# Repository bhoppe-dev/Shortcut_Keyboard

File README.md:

# Shortcut Keyboard

A programmable macro keyboard project featuring 8 customizable keys and a rotary encoder for volume control. Built with an RP2040 microcontroller and Cherry MX switches.

<p align="center">
  
  <br>
  <em>Shortcut Keyboard PCB</em>
</p>

## Features

- 8 programmable macro keys with Cherry MX switches (Blue or Brown)
- Rotary encoder with push button for volume control/mute
- USB-C connectivity
- RP2040 microcontroller
- CircuitPython firmware
- Windows compatibility
- Up to 3 different profiles for key configurations
- No additional drivers required

## Specifications

| Parameter | Value |
|-----------|-------|
| Input Voltage | 4.75-5.25V (USB) |
| Operating Current | ~50mA |
| Operating Temperature | 0-85°C |
| PCB Dimensions | 100 x 79 mm |
| Switches | Cherry MX Blue/Brown |
| Communication | USB HID |
| MCU | RP2040 |
| Firmware | CircuitPython |

## Hardware

The keyboard consists of three PCBs:
1. Main board with RP2040 and components
2. Top plate
3. Bottom plate

### Key Switch Options

| Feature | MX Blue | MX Brown |
|---------|---------|----------|
| Actuation Force | 60 cN | 55 cN |
| Pre-travel | 2.2 mm | 2.0 mm |
| Total Travel | 4.0 mm | 4.0 mm |
| Characteristics | Tactile & Clicky | Tactile |
| Sound | Audible click | Silent |

## Software

> The source code is available on GitHub at [https://github.com/bhoppe-dev/ShortcutKeyboardApp](https://github.com/bhoppe-dev/ShortcutKeyboardApp).
> 
The software suite includes:
- Windows configuration application
- Three customizable profiles
- File/folder/application launch capabilities
- URL opening support
- System tray integration
- Dark mode support

<p align="center">
  
  <br>
  <em>Main Window</em>
</p>

<p align="center">
  
  <br>
  <em>Configuration Window</em>
</p>

## Firmware

The keyboard runs CircuitPython firmware with the following features:
- USB HID implementation
- Key debouncing
- Rotary encoder support
- Volume control integration
- Multiple profile support

## License

This project is licensed under the BSD 2-Clause License - see the LICENSE file for details.

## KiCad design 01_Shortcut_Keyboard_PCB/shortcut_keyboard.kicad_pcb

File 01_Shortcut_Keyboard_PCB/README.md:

# PCB Documentation

KiCad project files for the Shortcut-Keyboard PCB based on RP2040.

## RP2040 Interface Block Diagram
Interface overview of the used RP2040 microcontroller pins and buses:

<p align="center">
  
  <br>
  <em>RP2040 Microcontroller Interface</em>
</p>

## Directory Structure

### Folders
- `01_Schematic/` - Schematic exports and documentation
- `02_BOM/` - Bill of Materials and part lists
- `03_STEP/` - 3D models and mechanical files

### KiCad Files
- `shortcut_keyboard.kicad_pro` - Project file
- `shortcut_keyboard.kicad_sch` - Main schematic
- `shortcut_keyboard.kicad_pcb` - PCB layout
- `MCU.kicad_sch` - MCU specific schematic
- `Connector.kicad_sch` - Connector specific schematic
- `Revision_History.kicad_sch` - Version tracking

## Layer Stackup
This PCB uses a SIG/GND/VCC/SIG stackup instead of the more conventional SIG/GND/GND/SIG configuration. This decision was based on several design considerations:

1. **Design Optimization:** The chosen stackup provides an optimal balance between routing efficiency and performance for this specific application.

2. **Signal Requirements Analysis:** After analyzing the signal integrity requirements for the RP2040-based keyboard, I determined that the modest-speed signals don't demand the theoretical advantages of dual ground planes.

3. **Power Distribution:** The dedicated VCC plane on L3 provides sufficient power distribution for all components while simplifying the overall routing strategy.

4. **Manufacturing Considerations:** The SIG/GND/VCC/SIG configuration maintains the same manufacturing complexity while offering adequate electrical performance for this application.

5. **Application-Specific Design:** For this particular keyboard application, the SIG/GND/VCC/SIG arrangement meets all functional requirements while enabling a more streamlined development process.

## Specifications
- Size: 100 x 79 mm
- Layers: 4 layer, 1.6mm FR4
- Version: V1.00.01 (2025-02-02)
- KiCad Version: 8.0.7

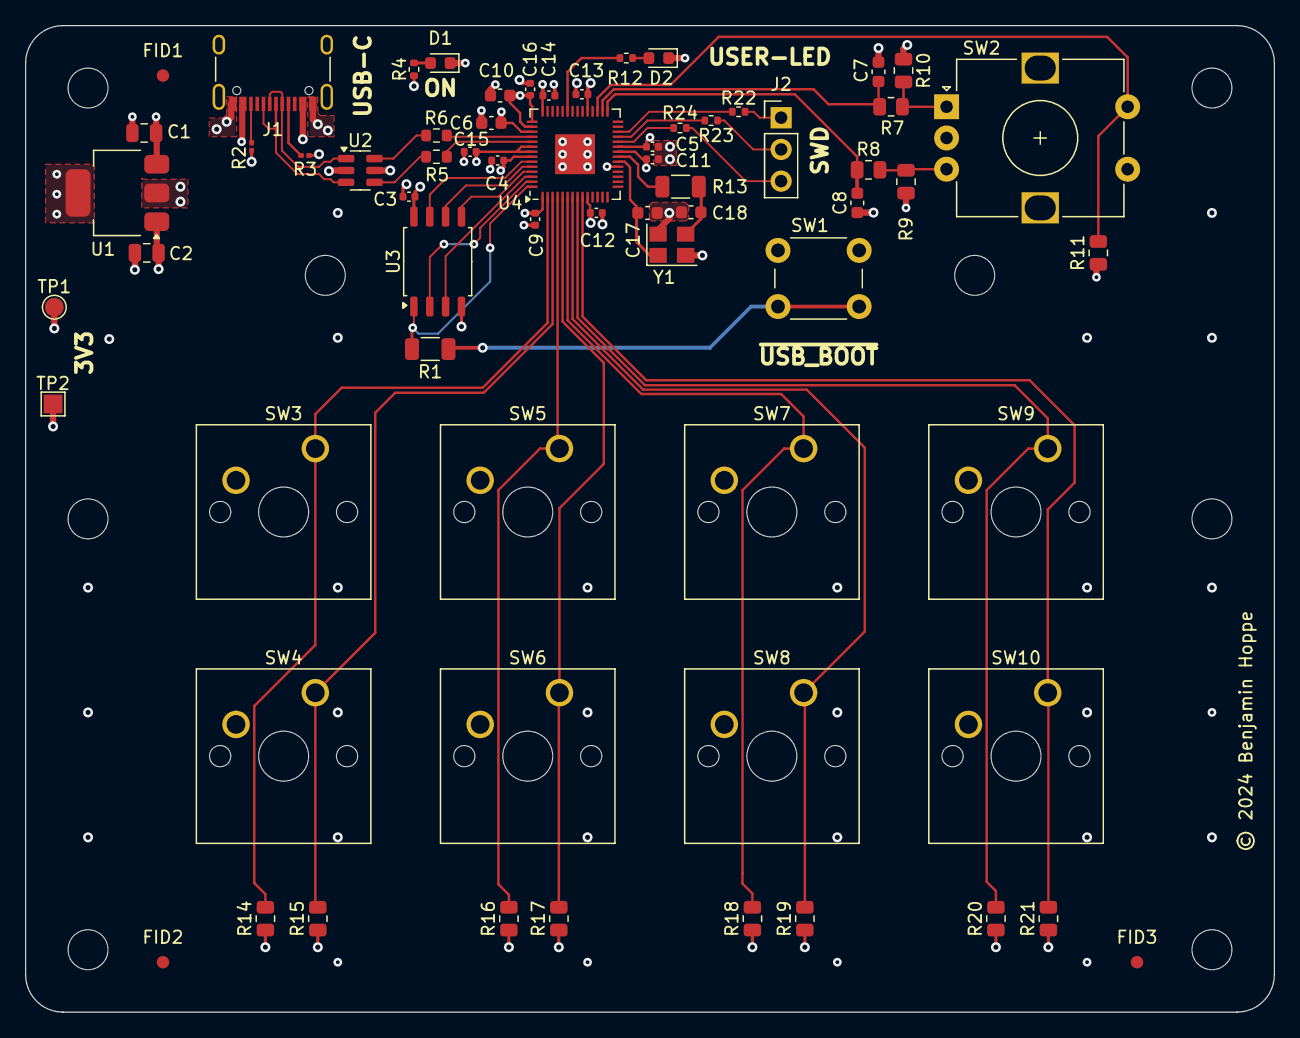
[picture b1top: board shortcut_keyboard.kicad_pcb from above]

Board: 4 copper layers, 100.0 x 79.0 mm, 74 parts (0 on the bottom side), 44 nets.

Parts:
C1, C2: 10uF; C_0805_2012Metric
C3, C4, C5, C9, C11, C12, C13, C14, C15, C16: 100nF; C_0402_1005Metric
C6, C10: 1uF; C_0603_1608Metric
C7, C8: 10nF; C_0603_1608Metric
C17, C18: 15pF; C_0603_1608Metric
D1: SML-D12Y8WT86R (yellow); LED_0603_1608Metric
D2: KT-0603R (red); LED_0603_1608Metric
FID1, FID2, FID3: Fiducial; Fiducial_1mm_Mask2mm
H1, H2, H3, H4, H5, H6, H7, H8: MountingHole; MountingHole_3.2mm_M3
J1: USB_C_Receptacle_USB2.0_16P; USB_C_Receptacle_XKB_U262-16XN-4BVC11
J2: Conn_01x03; PinHeader_1x03_P2.54mm_Vertical
R1, R13: 1k; R_1206_3216Metric
R2, R3: 5k1; R_0201_0603Metric
R4: 220; R_0402_1005Metric
R5, R6: 27; R_0603_1608Metric
R7, R8, R9, R10, R11, R14, R15, R16, R17, R18, R19, R20, R21: 10k; R_0805_2012Metric
R12: 470; R_0402_1005Metric
R22, R23, R24: 49R9; R_0402_1005Metric
SW1: SW_Push; SW_PUSH_6mm_H5mm
SW2: RotaryEncoder_Switch; RotaryEncoder_Alps_EC12E-Switch_Vertical_H20mm
SW3, SW4, SW5, SW6, SW7, SW8, SW9, SW10: SW_Push; SW_Cherry_MX_1.00u_PCB
TP1: TP_3V3; TestPoint_Pad_D1.5mm
TP2: TP_GND; TestPoint_Pad_1.5x1.5mm
U1: NCP1117-3.3_SOT223; SOT-223-3_TabPin2
U2: USBLC6-2SC6; SOT-23-6
U3: W25Q128JVS; SOIC-8_5.23x5.23mm_P1.27mm
U4: RP2040; QFN-56-1EP_7x7mm_P0.4mm_EP3.2x3.2mm
Y1: ABM8-272-T3; Crystal_SMD_3225-4Pin_3.2x2.5mm

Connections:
+1V1: C4.1, C5.1, C6.1, U4.23 (DVDD), U4.45 (VREG_VOUT), U4.50 (DVDD)
+3V3: C2.1, C3.1, C9.1, C10.1, C11.1, C12.1, C13.1, C14.1, C15.1, C16.1, R4.1, R9.1, R10.1, R11.1, R14.1, R15.1, R16.1, R17.1, R18.1, R19.1, R20.1, R21.1, TP1.1, U1.2 (VO), U3.8 (VCC), U4.1 (IOVDD), U4.10 (IOVDD), U4.22 (IOVDD), U4.33 (IOVDD), U4.42 (IOVDD), U4.43 (ADC_AVDD), U4.44 (VREG_IN), U4.48 (USB_VDD), U4.49 (IOVDD)
/Connector/Key1: R14.2, SW3.1, U4.2 (GPIO0)
/Connector/Key2: R15.2, SW4.1, U4.3 (GPIO1)
/Connector/Key3: R16.2, SW5.1, U4.4 (GPIO2)
/Connector/Key4: R17.2, SW6.1, U4.5 (GPIO3)
/Connector/Key5: R18.2, SW7.1, U4.6 (GPIO4)
/Connector/Key6: R19.2, SW8.1, U4.7 (GPIO5)
/Connector/Key7: R20.2, SW9.1, U4.8 (GPIO6)
/Connector/Key8: R21.2, SW10.1, U4.9 (GPIO7)
/MCU/ENC.A: R7.2, R10.2, SW2.A
/MCU/ENC.B: R8.2, R9.2, SW2.B
/MCU/ENCODER.A: C7.1, R7.1, U4.30 (GPIO19)
/MCU/ENCODER.B: C8.1, R8.1, U4.29 (GPIO18)
/MCU/ENCODERSW: R11.2, SW2.S1, U4.31 (GPIO20)
/MCU/QSPI.SCLK: U3.6 (CLK), U4.52 (QSPI_SCLK)
/MCU/QSPI.SD0: U3.5 (DI(IO0)), U4.53 (QSPI_SD0)
/MCU/QSPI.SD1: U3.2 (DO(IO1)), U4.55 (QSPI_SD1)
/MCU/QSPI.SD2: U3.3 (IO2), U4.54 (QSPI_SD2)
/MCU/QSPI.SD3: U3.7 (IO3), U4.51 (QSPI_SD3)
/MCU/QSPI.SS: R1.2, U3.1 (~CS), U4.56 (QSPI_SS)
/MCU/RUN: R22.1, U4.26 (RUN)
/MCU/RUN_CON: J2.1, R22.2
/MCU/SW.CLK: R24.1, U4.24 (SWCLK)
/MCU/SW.D: R23.1, U4.25 (SWD)
/MCU/SWCLK_CON: J2.3, R24.2
/MCU/SW_CON: J2.2, R23.2
/MCU/USBC_D+: J1.A6 (D+), J1.B6 (D+), U2.3 (I/O2)
/MCU/USBC_D-: J1.A7 (D-), J1.B7 (D-), U2.1 (I/O1)
/MCU/USB_CON_CC1: J1.A5 (CC1), R3.1
/MCU/USB_CON_CC2: J1.B5 (CC2), R2.1
/MCU/USB_D+: R5.1, U2.4 (I/O2)
/MCU/USB_D-: R6.1, U2.6 (I/O1)
/MCU/USER_LED: R12.1, U4.37 (GPIO25)
/MCU/XIN: C17.1, U4.20 (XIN), Y1.1
/MCU/XOUT: R13.2, U4.21 (XOUT)
/MCU/~USB_BOOT: R1.1, SW1.2
GND: C1.2, C2.2, C3.2, C4.2, C5.2, C6.2, C7.2, C8.2, C9.2, C10.2, C11.2, C12.2, C13.2, C14.2, C15.2, C16.2, C17.2, C18.2, D1.1 (K), D2.1 (K), J1.A1 (GND), J1.A12 (GND), J1.B1 (GND), J1.B12 (GND), J1.S1 (SHIELD), R2.2, R3.2, SW1.1, SW2.C, SW2.S2, SW3.2, SW4.2, SW5.2, SW6.2, SW7.2, SW8.2, SW9.2, SW10.2, TP2.1, U1.1 (GND), U2.2 (GND), U3.4 (GND), U4.19 (TESTEN), U4.57 (GND), Y1.2, Y1.4
unnamed: C18.1, R13.1, Y1.3
unnamed: D1.2 (A), R4.2
unnamed: D2.2 (A), R12.2
unnamed: R6.2, U4.46 (USB_DM)
unnamed: R5.2, U4.47 (USB_DP)
VBUS: C1.1, J1.A4 (VBUS), J1.A9 (VBUS), J1.B4 (VBUS), J1.B9 (VBUS), U1.3 (VI), U2.5 (VBUS)

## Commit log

2025-02-08 Rename 1739025690881_cut.jpg to Keyboard_TOP_Square_cut.jpg
2025-02-08 Rename 1739025690898_cut.jpg to Keyboard Top Square_Portrait_cut.jpg
2025-02-08 docs: Add initial README
    - Add comprehensive project description and features
    - Include hardware specifications and PCB details
    - Note status of upcoming C# configuration software
2025-02-08 Rename Keyboard Top Square_Portrait_cut.jpg to Keyboard_Top_Portrait_cut.jpg
2025-02-08 docs: Update keyboard PCB image in README
    Replace Keyboard_Top_Portrait_cut.jpg with Keyboard_TOP_Square_cut.jpg
2025-02-08 docs: Improve software preview image layout in README.md
    - Add separate captions for main and config windows
    - Adjust image widths for better visibility
2025-02-08 docs: README.md - Remove version information section
2025-02-09 renamed folder 03_Pictures to 04_Pictures
2025-02-09 Add enclosure design files
2025-02-09 doc: README.md new picture path
    - Rename the image folder
2025-02-09 docs(firmware): add firmware documentation README
2025-02-13 docs(pcb): add README with RP2040 interface block diagram
    Add PCB folder documentation with focus on RP2040 pin assignments and bus interfaces.
2025-02-13 feat(pcb): add pictures folder for documentation
2025-02-13 feat(pcb): add in pictures folder new blockdiagram
2025-02-13 docs(pcb): new SVG block diagram in README.md
2025-02-24 Update README with layer stackup explanation
2025-05-04 doc (README): Add link to in-progress software repository
2025-08-10 docs(README): update ShortcutKeyboardApp software now available
    - Remove "under development" and "coming soon" notices
    - Update image captions to remove "Preview" labels

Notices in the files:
01_Shortcut_Keyboard_PCB/shortcut_keyboard.kicad_pcb:
© 2024 Benjamin Hoppe
